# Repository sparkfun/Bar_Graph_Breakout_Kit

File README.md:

SparkFun Bar Graph Breakout Arduino Library
========================================

[*SparkFun Bar Graph Breakout Kit (DEV-10936)*](https://www.sparkfun.com/products/10936)

Arduino library that allows the user to control each LED in the bar graph, using both shift registers and 10-segment bargraph kits.

Repository Contents
-------------------

* **/examples** - Example sketches for the library (.ino). Run these from the Arduino IDE. 
* **/src** - Source files for the library (.cpp, .h).
* **keywords.txt** - Keywords from this library that will be highlighted in the Arduino IDE. 
* **library.properties** - General library properties for the Arduino package manager. 

Documentation
--------------

* **[Installing an Arduino Library Guide](https://learn.sparkfun.com/tutorials/installing-an-arduino-library)** - Basic information on how to install an Arduino library.
* **[Product Repository](https://github.com/sparkfun/Bar_Graph_Breakout_Kit)** - Main repository (including hardware files) for the Bar Graph Kit.
* **[Hookup Guide](http://cdn.sparkfun.com/datasheets/Kits/Bargraph%20Breakout%20Kit%20111227.pdf)** - Basic hookup guide for the Bar Graph Kit.

License Information
-------------------

This product is _**open source**_! 

The **code** is beerware; if you see me (or any other SparkFun employee) at the local, and you've found our code helpful, please buy us a round!

Please use, reuse, and modify these files as you see fit. Please maintain attribution to SparkFun Electronics and release anything derivative under the same license.

Distributed as-is; no warranty is given.

- Your friends at SparkFun.

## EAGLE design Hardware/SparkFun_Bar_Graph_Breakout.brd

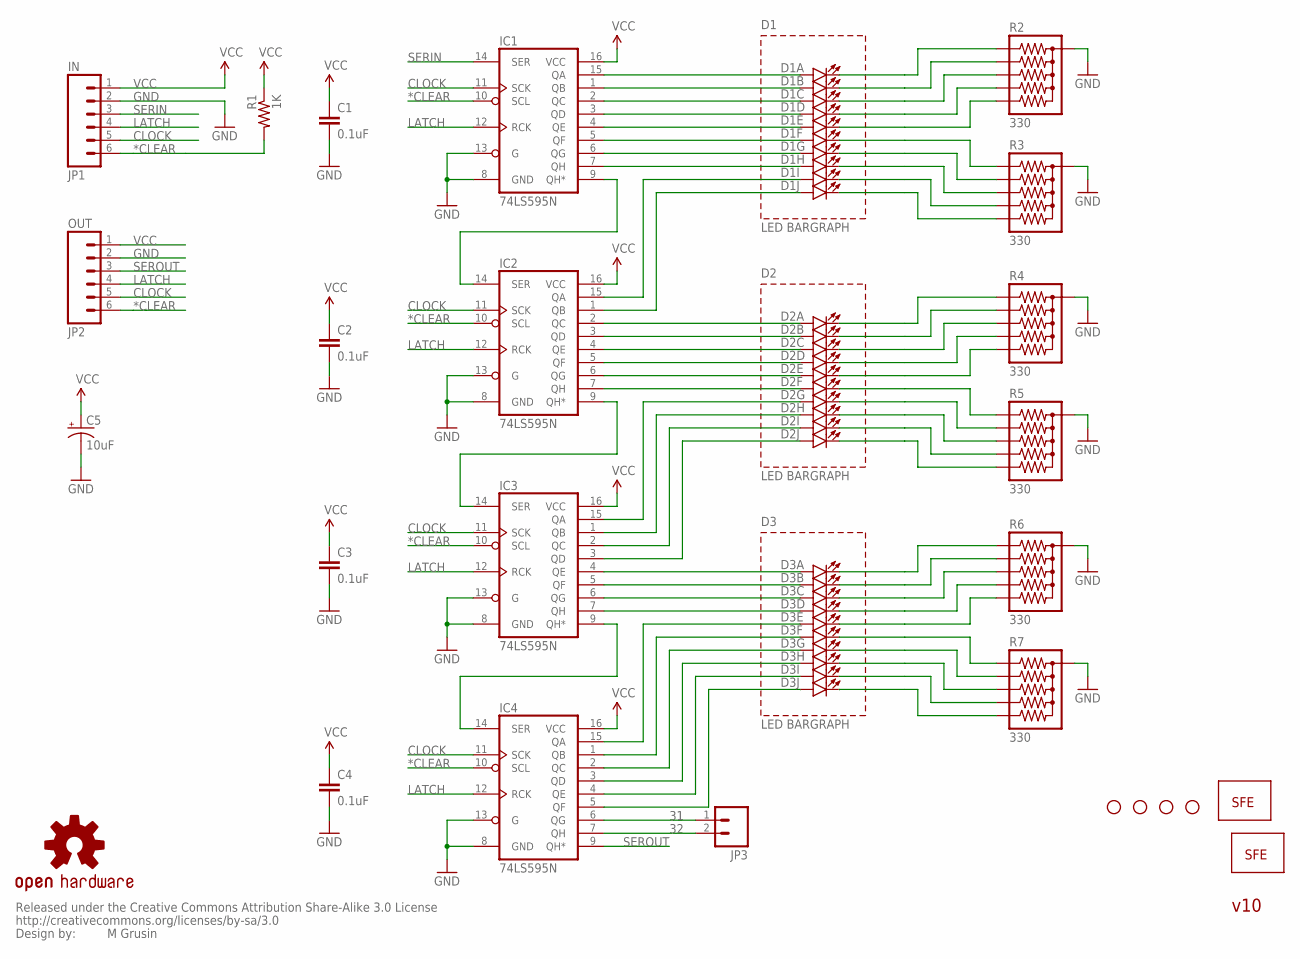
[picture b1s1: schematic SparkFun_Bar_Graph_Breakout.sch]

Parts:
C1, C2, C3, C4: 0.1uF; CAP-PTH-SMALL2
C5: 10uF; CPOL-RADIAL-10UF-25V
D1, D2, D3: LED_BARGRAPH_10; LED_BARGAPH_10
IC1, IC2, IC3, IC4: 74LS595N; DIL16
JP1: IN; 1X06
JP2: OUT; 1X06
JP3: M02PTH; 1X02
LOGO1: LOGO-SFENW2; SFE-NEW-WEB
LOGO2: LOGO-SFESK; SFE-LOGO-FLAME
R1: 1K; AXIAL-0.3
R2, R3, R4, R5, R6, R7: 330; RPACK-SIP-PTH-5
SO1, SO2, SO3, SO4: STAND-OFF
U$5: OSHW-LOGOM; OSHW-LOGO-M
U$6: CREATIVE_COMMONS

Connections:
31: IC4.6 (QG), JP3.1
32: IC4.7 (QH), JP3.2
*CLEAR: IC1.10 (SCL), IC2.10 (SCL), IC3.10 (SCL), IC4.10 (SCL), JP1.6, JP2.6, R1.P$2 (2)
CLOCK: IC1.11 (SCK), IC2.11 (SCK), IC3.11 (SCK), IC4.11 (SCK), JP1.5, JP2.5
GND: C1.2, C2.2, C3.2, C4.2, C5.2 (-), IC1.8 (GND), IC1.13 (G), IC2.8 (GND), IC2.13 (G), IC3.8 (GND), IC3.13 (G), IC4.8 (GND), IC4.13 (G), JP1.2, JP2.2, R2.P$1 (1), R3.P$1 (1), R4.P$1 (1), R5.P$1 (1), R6.P$1 (1), R7.P$1 (1)
LATCH: IC1.12 (RCK), IC2.12 (RCK), IC3.12 (RCK), IC4.12 (RCK), JP1.4, JP2.4
unnamed: D1.1 (A), IC1.15 (QA)
unnamed: D1.2 (A), IC1.1 (QB)
unnamed: D1.3 (A), IC1.2 (QC)
unnamed: D1.4 (A), IC1.3 (QD)
unnamed: D1.5 (A), IC1.4 (QE)
unnamed: D1.6 (A), IC1.5 (QF)
unnamed: D1.7 (A), IC1.6 (QG)
unnamed: D1.8 (A), IC1.7 (QH)
unnamed: D1.9 (A), IC2.15 (QA)
unnamed: D1.10 (A), IC2.1 (QB)
unnamed: D2.8 (A), IC3.1 (QB)
unnamed: D2.7 (A), IC3.15 (QA)
unnamed: D2.9 (A), IC3.2 (QC)
unnamed: D2.10 (A), IC3.3 (QD)
unnamed: D3.1 (A), IC3.4 (QE)
unnamed: D3.2 (A), IC3.5 (QF)
unnamed: D3.3 (A), IC3.6 (QG)
unnamed: D3.4 (A), IC3.7 (QH)
unnamed: D2.1 (A), IC2.2 (QC)
unnamed: D2.2 (A), IC2.3 (QD)
unnamed: D2.3 (A), IC2.4 (QE)
unnamed: D2.4 (A), IC2.5 (QF)
unnamed: D2.5 (A), IC2.6 (QG)
unnamed: D2.6 (A), IC2.7 (QH)
unnamed: D1.20 (C), R2.P$2 (2)
unnamed: D1.19 (C), R2.P$3 (3)
unnamed: D3.5 (A), IC4.15 (QA)
unnamed: D3.6 (A), IC4.1 (QB)
unnamed: D1.18 (C), R2.P$4 (4)
unnamed: D1.17 (C), R2.P$5 (5)
unnamed: D1.16 (C), R2.P$6 (6)
unnamed: D1.15 (C), R3.P$2 (2)
unnamed: D1.14 (C), R3.P$3 (3)
unnamed: D1.13 (C), R3.P$4 (4)
unnamed: D1.12 (C), R3.P$5 (5)
unnamed: D1.11 (C), R3.P$6 (6)
unnamed: D2.20 (C), R4.P$2 (2)
unnamed: D2.19 (C), R4.P$3 (3)
unnamed: D3.7 (A), IC4.2 (QC)
unnamed: D3.8 (A), IC4.3 (QD)
unnamed: D3.9 (A), IC4.4 (QE)
unnamed: D3.10 (A), IC4.5 (QF)
unnamed: D2.18 (C), R4.P$4 (4)
unnamed: D2.17 (C), R4.P$5 (5)
unnamed: D2.16 (C), R4.P$6 (6)
unnamed: D2.15 (C), R5.P$2 (2)
unnamed: D2.14 (C), R5.P$3 (3)
unnamed: D2.13 (C), R5.P$4 (4)
unnamed: D2.12 (C), R5.P$5 (5)
unnamed: D2.11 (C), R5.P$6 (6)
unnamed: D3.20 (C), R6.P$2 (2)
unnamed: D3.19 (C), R6.P$3 (3)
unnamed: D3.18 (C), R6.P$4 (4)
unnamed: D3.17 (C), R6.P$5 (5)
unnamed: D3.16 (C), R6.P$6 (6)
unnamed: D3.15 (C), R7.P$2 (2)
unnamed: D3.14 (C), R7.P$3 (3)
unnamed: D3.13 (C), R7.P$4 (4)
unnamed: D3.12 (C), R7.P$5 (5)
unnamed: D3.11 (C), R7.P$6 (6)
unnamed: IC1.9 (QH*), IC2.14 (SER)
unnamed: IC2.9 (QH*), IC3.14 (SER)
unnamed: IC3.9 (QH*), IC4.14 (SER)
SERIN: IC1.14 (SER), JP1.3
SEROUT: IC4.9 (QH*), JP2.3
VCC: C1.1, C2.1, C3.1, C4.1, C5.1 (+), IC1.16 (VCC), IC2.16 (VCC), IC3.16 (VCC), IC4.16 (VCC), JP1.1, JP2.1, R1.P$1 (1)

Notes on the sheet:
M Grusin
LED BARGRAPH
v10

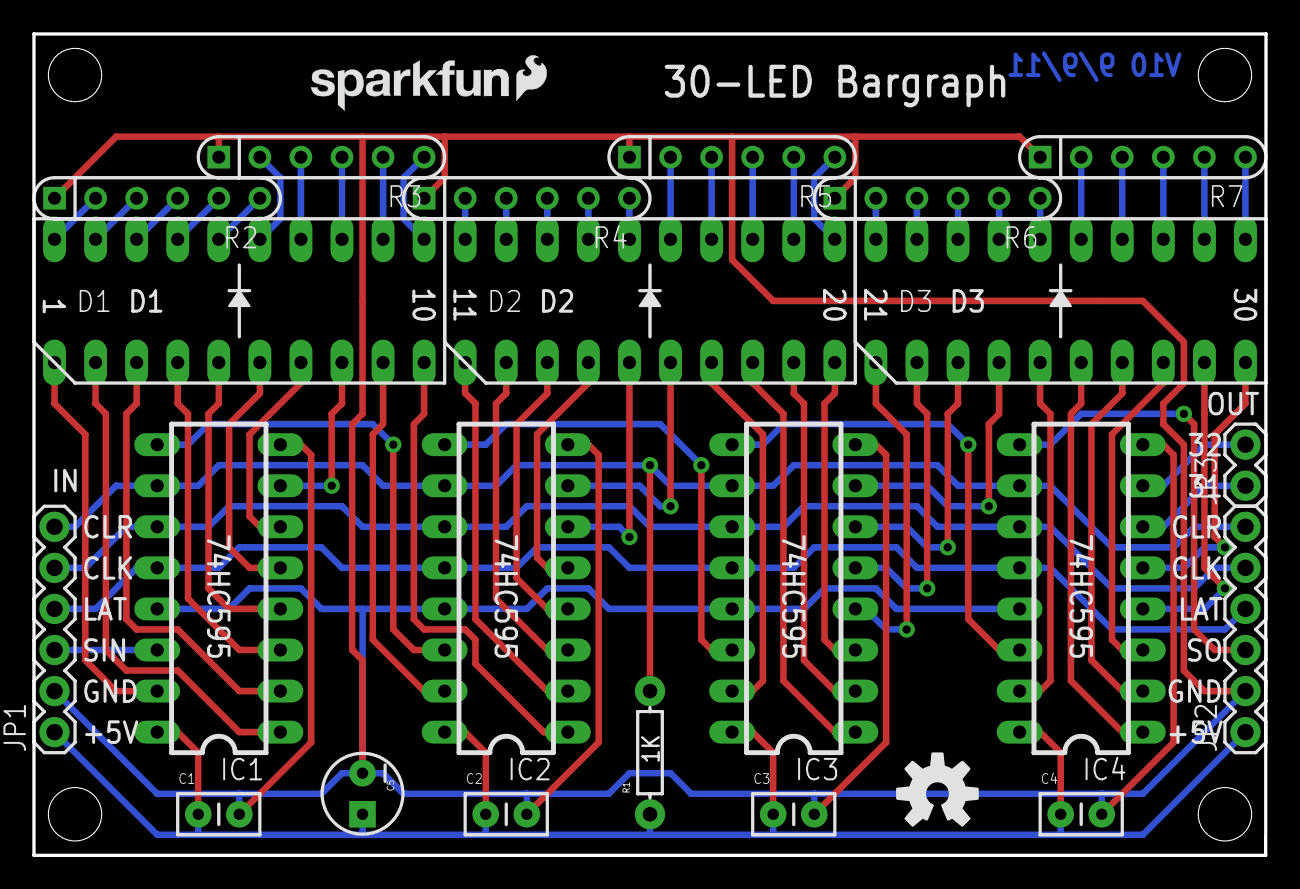
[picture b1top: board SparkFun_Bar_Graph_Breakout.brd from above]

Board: 2 copper layers, 76.2 x 50.8 mm, 30 parts (0 on the bottom side), 72 nets.

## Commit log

2015-05-12 Adding hardware files, updating readme
2015-05-12 Squashed 'Libraries/Arduino/' content from commit 0776c9f
    git-subtree-dir: Libraries/Arduino
    git-subtree-split: 0776c9f32d622c4968be7ee5424f1dbd90832184
2015-05-12 Updating subtree directions on library

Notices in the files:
parts and their libraries:
SparkFun: Released under the Creative Commons Attribution Share-Alike 3.0 License
SparkFun: http://creativecommons.org/licenses/by-sa/3.0
